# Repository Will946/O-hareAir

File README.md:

# O'Hare Air

A desktop air quality monitor shaped like a flower. It watches temperature, humidity, and air quality (eCO2/eTVOC/AQI-UBA) with a ScioSense ENS161 + ENS210, points a physical stepper-driven needle at the current rating, glows green-to-red through an RGB LED, and serves a full live dashboard over Wi-Fi with history and CSV export. No app, no cloud, no account.

---

## Where the name comes from

The name is taken from The Lorax (2012). In the film, Aloysius O'Hare is the mayor of Thneedville and the founder/CEO of "O'Hare Air," a company that sells bottled air to the town after industrial pollution ruined the natural air supply. This project borrows the name "O'Hare Air" for a device that measures real air quality.

---

## Table of contents

- [Features](#features)
- [How it all fits together](#how-it-all-fits-together)
- [Hardware — two PCB generations](#hardware--two-pcb-generations)
  - [V1 — ESP32-S3 dev-board shield](#v1--esp32-s3-dev-board-shield)
  - [V2 — custom ESP32-H2 module board](#v2--custom-esp32-h2-module-board)
  - [V1 vs V2 at a glance](#v1-vs-v2-at-a-glance)
- [Firmware](#firmware)
  - [Startup and timing](#startup-and-timing)
  - [How air quality is measured and calculated](#how-air-quality-is-measured-and-calculated)
  - [Temperature and humidity](#temperature-and-humidity)
  - [The needle](#the-needle)
  - [The LED](#the-led)
  - [History logging](#history-logging)
- [The web dashboard](#the-web-dashboard)
- [Flashing it yourself](#flashing-it-yourself)
- [Known limitations](#known-limitations)

---

## Features

- **Real air-quality sensing**: ScioSense ENS161 (eTVOC, eCO2, and an onboard 1-5 AQI-UBA rating) plus an ENS210 for temperature and humidity.
- **A physical gauge**: a 28BYJ-48 stepper motor sweeps a needle from 0° to 180° across five ratings: Excellent, Good, Moderate, Poor, Unhealthy.
- **A living LED**: a smooth green-to-red gradient that tracks the current rating, and a slow blue pulse while the sensor is still warming up.
- **A full web dashboard**: live readings, up to seven days of on-device history with min/avg/max, CSV export, and manual needle/LED control, all served directly from the board over Wi-Fi.
- **Two hardware generations**: a shield that plugs onto an off-the-shelf ESP32-S3 dev board (V1), and a from-scratch, coin-sized board built around a bare ESP32-H2 module (V2).
- **A 3D-printed flower enclosure**, because an air monitor sitting on your desk should look like it belongs there.

---

## How it all fits together

```
        ENS210 (temp/RH) ──┐
                            ├──► ESP32 ──► 28BYJ-48 stepper ──► needle (0°-180°)
        ENS161 (AQI-UBA,   ─┘      │
        eTVOC, eCO2)               ├──► RGB LED (green → yellow → orange → red)
                                    │
                                    └──► Wi-Fi ──► built-in web dashboard
                                              (Live / History / Needle tabs)
```

Both sensors sit on the same I2C bus. Every reading cycle, the firmware pulls temperature and humidity from the ENS210, feeds them to the ENS161 as environmental compensation (metal-oxide gas sensors need to know how hot and humid the air is to interpret resistance changes correctly), then reads the ENS161's eTVOC, eCO2, and AQI-UBA registers. AQI-UBA, the sensor's own 1-5 classification, is what drives the needle and the LED. Everything is also pushed out over the board's Wi-Fi web server so it's watchable from a phone or laptop in real time.

---

## Hardware — two PCB generations

### V1 — ESP32-S3 dev-board shield

V1 is a **shield**: a round board with two 2×22 headers (`J9`/`J10`) that plug directly onto an **ESP32-S3-DevKitC-1** dev board, using its pinout exactly. Rather than design a whole MCU circuit, V1 borrows the dev board's regulator, USB-to-serial bridge, and antenna, so the custom PCB only has to carry the sensors, the LED driver, and a 1.8 V rail.

**On the shield itself:**

| Ref | Part | Purpose |
|---|---|---|
| U1 | ENS161-BLGT | Air quality sensor (I2C `0x52`), eTVOC, eCO2, AQI-UBA |
| U2 | ENS210-LQFM | Temperature/humidity sensor (I2C `0x43`) |
| U3 | MCP1700T-1802E | Linear regulator, 3.3 V → 1.8 V for the ENS161's `VDD` rail |
| R1, R2 | 10 kΩ | I2C pull-ups (SCL/SDA) |
| C1–C6 | 0.1 µF / 10 µF | Decoupling for the sensors and the LED |
| Q1 | BSS138 | N-MOSFET level shifter, 3.3 V logic → 5 V for the LED data line |
| LED1 | IN-PI15TAT5R5G5B | A single addressable RGB LED |
| J1 | 3-pin socket | Breaks out 5 V / 3.3 V / LED data for the LED module |
| H1–H3, TP1 | — | Mounting holes and a test point |

The two headers expose every GPIO the dev board offers, but the sketch only actually uses a handful of them: `GPIO8`/`GPIO9` for I2C, `GPIO4`–`GPIO7` for the stepper's four ULN2003 driver inputs, and `GPIO48` for the dev board's own onboard RGB LED. 

Full schematic: [`OhareV1PCB/OhareV1Sch.pdf`](OhareV1PCB/OhareV1Sch.pdf). Manufacturing files (Gerbers) are in [`OhareV1PCB/Gerber.zip`](OhareV1PCB/Gerber.zip); KiCad source is [`OhareV1.kicad_pcb`](OhareV1PCB/OhareV1.kicad_pcb) / [`OhareV1.kicad_sch`](OhareV1PCB/OhareV1.kicad_sch).

### V2 — custom ESP32-H2 module board

V2 throws out the dev board entirely. Instead of two headers plugging into someone else's board, V2 puts an **ESP32-H2-MINI-1** module (a tiny, low-power Espressif module, not a full development board) directly on the PCB, along with its own USB-C connector and its own power regulation. The result is dramatically smaller: the whole "computer" fits in the footprint of the module itself, not a full dev-board-shaped hole in the middle of the design.

**On the V2 board:**

| Ref | Part | Purpose |
|---|---|---|
| U7 | ESP32-H2-MINI-1 | The microcontroller: BLE + 802.15.4 (Zigbee/Thread) radio, **no Wi-Fi** (see below) |
| U2 | ENS161 | Air quality sensor (I2C `0x52`) |
| U10 | ENS210 | Temperature/humidity sensor (I2C `0x43`) |
| U6 | AP2205 | 3.3 V regulator (the board's main "3V3 bus") |
| U5 | AP2120 | 1.8 V regulator, for the ENS161's `VDD` |
| P1 | USB-C receptacle | Power and native USB flashing (the H2 has built-in USB, no separate USB-serial chip needed) |
| D5 | TPD1E10B06 | ESD/surge protection on the USB data lines |
| R21, R22 | 5.1 kΩ | USB-C CC pull-downs, so the board correctly identifies itself as a 5 V sink to chargers and power banks |
| Q1 | BSS138 | Same level-shifting job as V1: 3.3 V logic to 5 V LED data |
| LED1, LED2, LED3 | IN-PI15TAT5R5G5B | **Three** addressable RGB LEDs (labeled Front Left / Front Right / Rear Right on the silkscreen), daisy-chained, instead of V1's single LED |
| S2 | Push button | BOOT (bootloader entry for flashing) |
| S3 | Push button | Reset |

Full schematic: [`OhareV2PCB/OhareV2Sch.pdf`](OhareV2PCB/OhareV2Sch.pdf); KiCad source is [`OhareV2.kicad_pcb`](OhareV2PCB/OhareV2.kicad_pcb) / [`OhareV2.kicad_sch`](OhareV2PCB/OhareV2.kicad_sch).

### V1 vs V2 at a glance

| | V1 | V2 |
|---|---|---|
| MCU | ESP32-S3-DevKitC-1 (full dev board, plugged in via headers) | ESP32-H2-MINI-1 (bare module, soldered directly to the PCB) |
| Radio | Wi-Fi + BLE | BLE + 802.15.4 (Zigbee/Thread); no Wi-Fi |
| Size | Dev-board-sized | A fraction of that; the module is the board |
| Power in | Through the dev board's own USB-C | Native USB-C directly on the PCB |
| LEDs | 1 (drives the dev board's onboard LED) | 3, individually placed under the enclosure's petals |
| Flashing | Dev board's onboard USB-to-serial bridge | Native USB on the H2 itself |
| Firmware status | **Fully supported**, this is what the current sketch targets | **Current firmware is supported on new version |

---

## Firmware

The active firmware is [`Code/OhareAir/OhareAir.ino`](Code/OhareAir/OhareAir.ino), an Arduino sketch built for the **ESP32-S3 (V1)**. It's written directly against the ENS161 and ENS210 datasheets: talking to both sensors over I2C, driving the stepper needle and RGB LED, and serving the whole web dashboard, all from a single self-contained sketch.

### Startup and timing

On power-up, both sensors initialize immediately, but **nothing is read for the first 3 minutes.** The ENS161 needs that long to reach a stable operating temperature; reading it earlier just produces noise. During this warm-up the LED pulses a slow blue instead of showing a color it can't back up yet, and the needle stays parked at 0°.

Once warm-up ends, the firmware takes **one reading per minute**. A flower on a desk doesn't need second-by-second air-quality updates, and a slower cadence keeps the I2C bus quieter.

Each reading cycle:
1. Read temperature and humidity from the ENS210.
2. Write those values to the ENS161's compensation registers (`TEMP_IN` / `RH_IN`), so its gas readings account for the current conditions.
3. Give the ENS161 a moment to fold that compensation into its next internal measurement.
4. Read eTVOC, eCO2, and AQI-UBA off the ENS161.
5. Feed everything into the 5-minute history accumulator.
6. If Auto mode is on, hand AQI-UBA to the needle logic.

### How air quality is measured and calculated

The ENS161 is a metal-oxide gas sensor: it doesn't count individual VOC molecules, it measures how much a heated sensing element's electrical resistance shifts when exposed to reactive gases, then converts that into three numbers over I2C:

- **eTVOC** (equivalent Total Volatile Organic Compounds, in ppb): the chip's estimate of total VOC concentration, calibrated against ethanol as a reference gas. This is the sensor's actual measurement; everything else is derived from it.
- **eCO2** (equivalent CO2, in ppm): not a real CO2 measurement. It's estimated from the same VOC signal, so it tracks eTVOC almost exactly and should be read as "how stale does the air smell," not literal CO2 concentration.
- **AQI-UBA** (1-5): the chip's own onboard hygienic rating, computed internally by ScioSense's proprietary algorithm from its eTVOC signal, using threshold bands published by Germany's Federal Environmental Agency (Umweltbundesamt, hence "UBA"):

  | AQI-UBA | Rating | Approx. eTVOC |
  |---|---|---|
  | 1 | Excellent | 0 – 65 ppb |
  | 2 | Good | 65 – 220 ppb |
  | 3 | Moderate | 220 – 650 ppb |
  | 4 | Poor | 650 – 2,200 ppb |
  | 5 | Unhealthy | 2,200 ppb+ |

**AQI-UBA is what drives the needle and the LED**, rather than a hand-built formula. eTVOC and eCO2 are still read, displayed, and logged, but the rating itself comes straight from the ENS161's own proprietary onboard algorithm: ScioSense's classification, computed inside the chip from its own internal, self-compensating signal, not something calculated in software afterward. The trade-off is that AQI-UBA can't be corrected or offset after the fact the way a software-calculated number could; whatever the chip decides, the firmware trusts.

### Temperature and humidity

Raw ENS210 output is corrected by a fixed offset (`TEMP_OFFSET_C`, currently 5.56 °C) to account for the board's own self-heating from the MCU and Wi-Fi radio; an uncorrected reading on this hardware runs noticeably warmer than the actual room. This is a per-board constant; if you build your own, re-measure it against a reference thermometer and adjust.

### The needle

A 28BYJ-48 stepper motor (through a ULN2003 driver board) sweeps a needle across a 180° arc:

| Rating | Angle |
|---|---|
| Excellent | 0° |
| Good | 90° |
| Moderate | 115° |
| Poor | 140° |
| Unhealthy | 180° |

To avoid the needle twitching back and forth when AQI-UBA hovers right at a boundary, a new rating has to show up in **two readings in a row** (about two minutes) before the needle actually moves. Position is tracked in software as a step count from a zeroed home position. There's no physical limit switch, so the needle has to be manually set to 0° before every power-up; if the board resets while the needle is elsewhere, the software's idea of "0°" and the needle's real position will disagree until it's re-zeroed by hand.

### The LED

The LED (a single onboard RGB LED on V1; three chained LEDs, wired for that, on V2's hardware) fades smoothly between colors rather than snapping: green at AQI-UBA 1, sliding through yellow and orange, to red at AQI-UBA 5. During warm-up, before any reading exists, it pulses a slow blue instead. Brightness (0/10/30/60/100%) is adjustable from the dashboard and resets to 60% on every reboot; it isn't saved to flash.

### History logging

Every 5 minutes, the firmware saves one entry (the minimum, average, and maximum of temperature, humidity, AQI-UBA, eCO2, and eTVOC over that window) into a ring buffer sized for **7 days** (2,016 entries), packed into a fixed 32-byte record per entry. **This history lives entirely in RAM, not flash**; it's lost on every reboot or power cycle. A window where a sensor read failed is stored as an explicit "no data" marker rather than a guessed value, so a bad reading never silently drags down an average.

---

## The web dashboard

The board runs its own web server (`WebServer.h`) and serves a self-contained single-page dashboard: no external app, no cloud round-trip. Connect it to Wi-Fi, open its IP address in a browser, and you get three tabs:

**Live**

The current AQI-UBA rating as a big color-coded number and name, a five-segment scale showing where it sits, temperature/humidity/eCO2/eTVOC cards, and three live-updating charts (temperature & humidity, AQI-UBA, and gas levels) that add one point per new reading, not per page refresh, so leaving the tab open doesn't flood the chart with duplicate points. LED brightness controls live here too.

**History**

The same charts, but built from the on-device 5-minute history instead of the live buffer, with a range selector (6 hours to 7 days) and CSV export.

**Needle**

Manual control: an Auto/Manual toggle, a reference table of which AQI-UBA rating maps to which angle, one-tap "go to angle" buttons for each rating, a free-form rotate-by-degrees input, and motor speed adjustment.

**Endpoints**, for anyone scripting against it directly:

| Endpoint | Purpose |
|---|---|
| `GET /status` | Current reading, needle state, and device status as JSON |
| `GET /history?n=N` | The newest N history entries as compact JSON |
| `GET /rotate?degrees=X` | Rotate the needle by X° (switches to Manual) |
| `GET /goto?degrees=X` | Move the needle to an absolute angle (switches to Manual) |
| `GET /mode?auto=0\|1` | Switch between Auto and Manual |
| `GET /speed?direction=faster\|slower` | Adjust stepper speed |
| `GET /brightness?pct=X` | Set LED brightness, 0–100 |

---

## Flashing it yourself

1. Arduino IDE with the ESP32 board package installed, targeting an ESP32-S3 board (V1 hardware).
2. Install the **Adafruit NeoPixel** library. `Wire`, `WiFi`, and `WebServer` ship with the ESP32 core.
3. Open [`Code/OhareAir/OhareAir.ino`](Code/OhareAir/OhareAir.ino) and fill in your Wi-Fi credentials:
```cpp
   const char* ssid = "";
   const char* password = "";
```
4. Flash it, then open the Serial Monitor at 115200 baud; it prints the board's IP address once connected.
5. Set the needle to its physical 0° position before powering on, since the firmware has no way to detect where it actually is.
6. Open that IP address in a browser on the same network.

---

## Known limitations

- **Highly temperature- and humidity-dependent.** The ENS161 is a metal-oxide gas sensor: its readings shift with the temperature and humidity it's told to compensate for, and the board's own self-heating (from the MCU and Wi-Fi radio) pushes the ENS210's raw temperature well above the actual room temperature. That's corrected with a fixed offset (`TEMP_OFFSET_C`) tuned for this specific board; a different enclosure, a different MCU, or even just a different ambient environment can shift the true offset enough that eTVOC, eCO2, and AQI-UBA all read differently than they would with perfect compensation.
- **History doesn't survive a reboot.** It's RAM-only; a power cycle clears it.
- **The needle has no home sensor.** It has to be manually zeroed before every power-up.
- **Wi-Fi credentials are hardcoded** in the sketch, not configurable from the dashboard.
- **No OTA updates**: reflashing means plugging in over USB, which means having to disassemble the enclosure to access the port.

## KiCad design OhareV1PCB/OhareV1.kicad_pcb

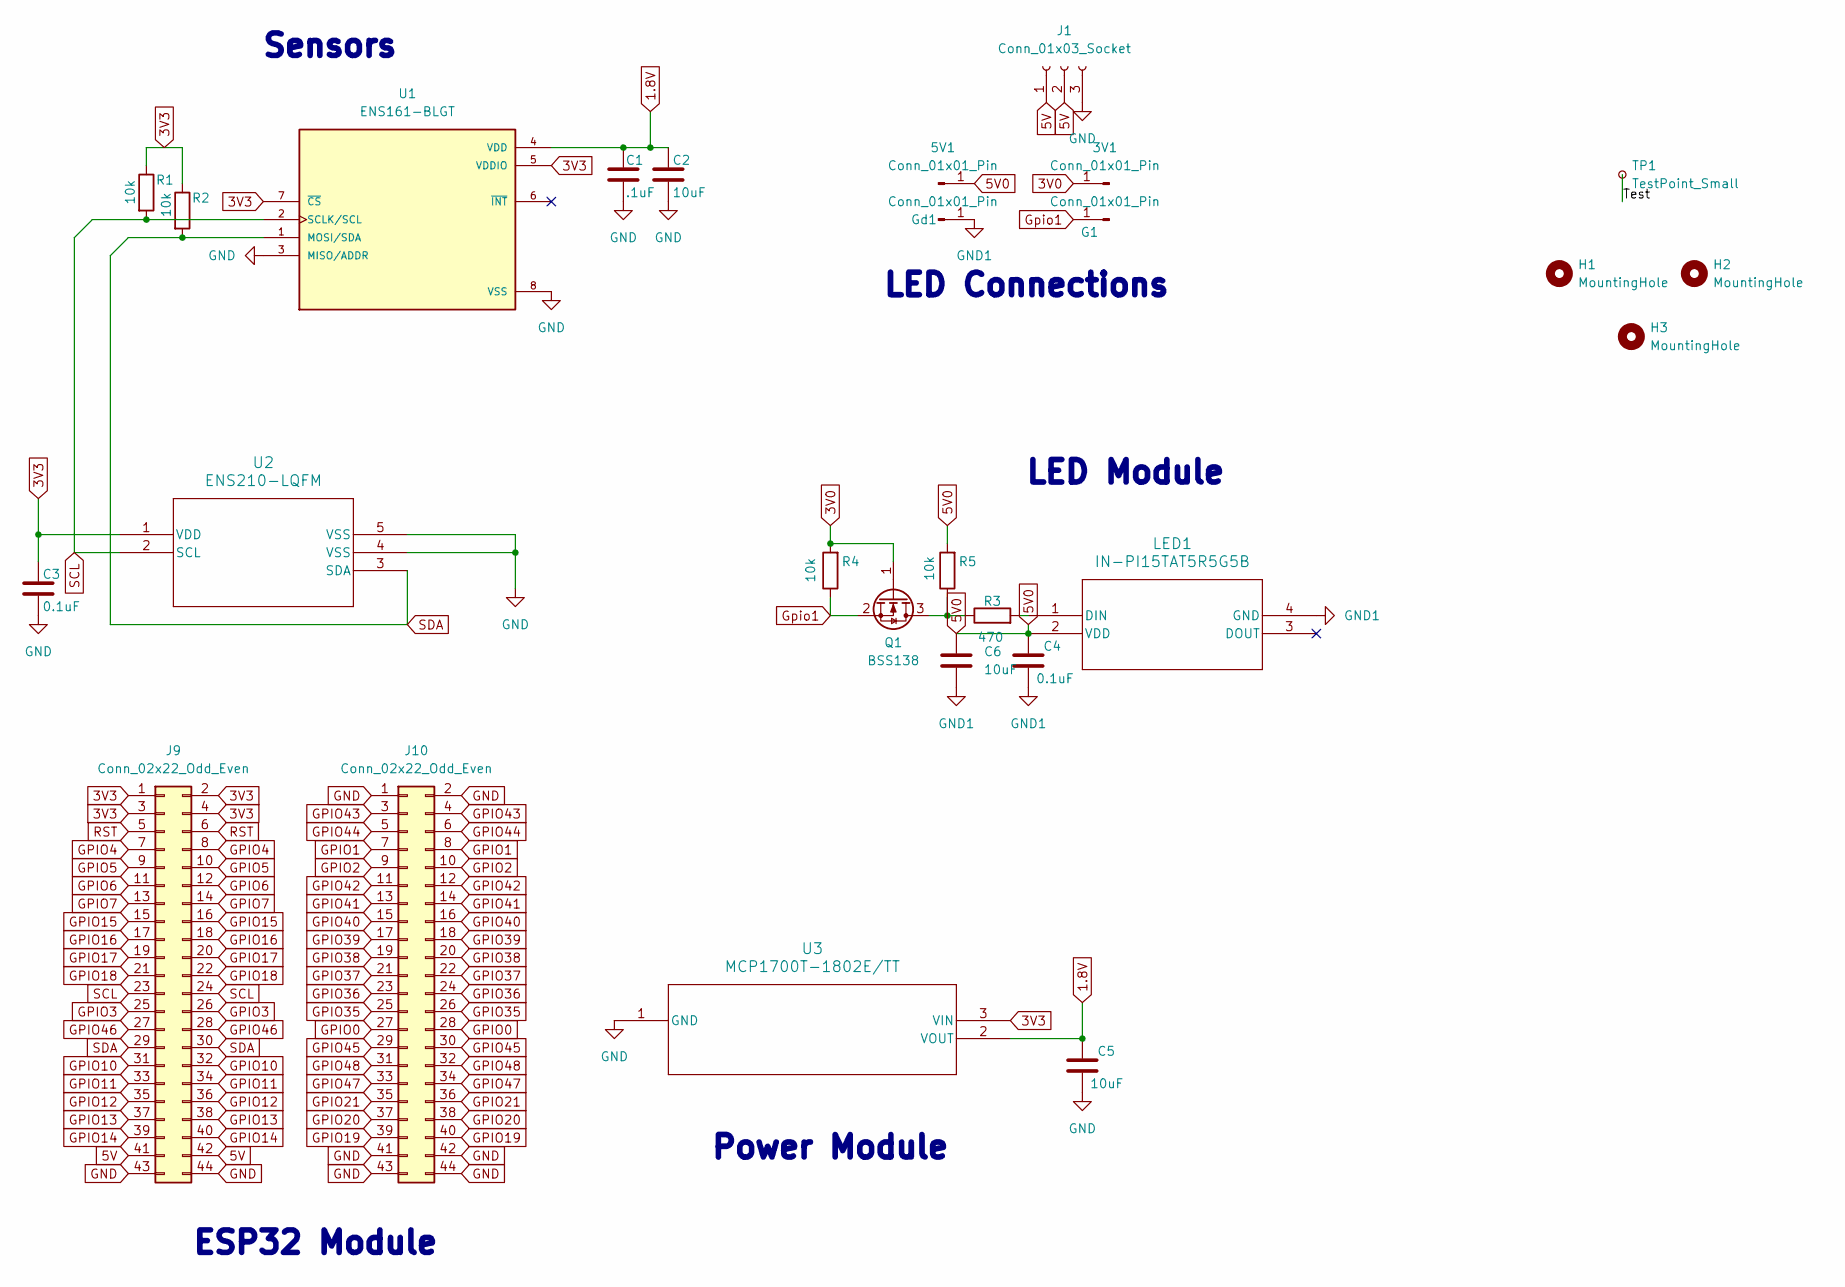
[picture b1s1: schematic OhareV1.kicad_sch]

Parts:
3V1, 5V1: Conn_01x01_Pin; PinHeader_1x01_P1.27mm_Vertical
C1: .1uF; C_0805_2012Metric_Pad1.18x1.45mm_HandSolder
C2, C5, C6: 10uF; C_0805_2012Metric_Pad1.18x1.45mm_HandSolder
C3, C4: 0.1uF; C_0805_2012Metric_Pad1.18x1.45mm_HandSolder
G1: Conn_01x01_Pin; PinHeader_1x01_P1.27mm_Vertical
Gd1: Conn_01x01_Pin; PinHeader_1x01_P1.27mm_Vertical
H1, H2, H3: MountingHole; MountingHole_3.2mm_M3
J1: Conn_01x03_Socket; PinHeader_1x03_P1.27mm_Vertical
J9, J10: Conn_02x22_Odd_Even; PinHeader_2x22_P2.54mm_Vertical
LED1: IN-PI15TAT5R5G5B; IN-PI15_INL
Q1: BSS138; SOT-23_3L_ONS-L
R1, R2, R4, R5: 10k; R_0805_2012Metric_Pad1.20x1.40mm_HandSolder
R3: 470; R_0805_2012Metric_Pad1.20x1.40mm_HandSolder
TP1: TestPoint_Small; TestPoint_Pad_1.0x1.0mm
U1: ENS161-BLGT; XDCR_ENS161-BLGT; PARTREV 1.3; DigiKey_Part_Number 2618-ENS161-BLGTCT-ND
U2: ENS210-LQFM; SON-04-ENS210_2X2_AMS-L
U3: MCP1700T-1802E/TT; SOT-23_MC_MCH-L

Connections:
1.8V: C1.1, C2.1, C5.1, U1.4 (VDD), U3.2 (VOUT)
3V0: 3V1.1, Q1.1 (G), R4.2
3V3: C3.1, J9.1, J9.2, J9.3, J9.4, R1.1, R2.1, U1.5 (VDDIO), U1.7 (~CS), U2.1 (VDD), U3.3 (VIN)
5V: J1.1, J1.2, J9.41, J9.42
5V0: 5V1.1, C4.1, C6.1, LED1.2 (VDD), R5.2
/Test: TP1.1
GND: C1.2, C2.2, C3.2, C5.2, J1.3, J9.43, J9.44, J10.1, J10.2, J10.41, J10.42, J10.43, J10.44, U1.3 (MISO/ADDR), U1.8 (VSS), U1.9 (VSS), U2.4 (VSS), U2.5 (VSS), U3.1 (GND)
GND1: C4.2, C6.2, Gd1.1, LED1.4 (GND)
GPIO0: J10.27, J10.28
GPIO1: J10.7, J10.8
GPIO2: J10.9, J10.10
GPIO3: J9.25, J9.26
GPIO4: J9.7, J9.8
GPIO5: J9.9, J9.10
GPIO6: J9.11, J9.12
GPIO7: J9.13, J9.14
GPIO10: J9.31, J9.32
GPIO11: J9.33, J9.34
GPIO12: J9.35, J9.36
GPIO13: J9.37, J9.38
GPIO14: J9.39, J9.40
GPIO15: J9.15, J9.16
GPIO16: J9.17, J9.18
GPIO17: J9.19, J9.20
GPIO18: J9.21, J9.22
GPIO19: J10.39, J10.40
GPIO20: J10.37, J10.38
GPIO21: J10.35, J10.36
GPIO35: J10.25, J10.26
GPIO36: J10.23, J10.24
GPIO37: J10.21, J10.22
GPIO38: J10.19, J10.20
GPIO39: J10.17, J10.18
GPIO40: J10.15, J10.16
GPIO41: J10.13, J10.14
GPIO42: J10.11, J10.12
GPIO43: J10.3, J10.4
GPIO44: J10.5, J10.6
GPIO45: J10.29, J10.30
GPIO46: J9.27, J9.28
GPIO47: J10.33, J10.34
GPIO48: J10.31, J10.32
Gpio1: G1.1, Q1.2 (S), R4.1
unnamed: LED1.1 (DIN), R3.2
unnamed: Q1.3 (D), R3.1, R5.1
RST: J9.5, J9.6

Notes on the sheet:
LED Connections
ESP32 Module
LED Module
Power Module
Sensors

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
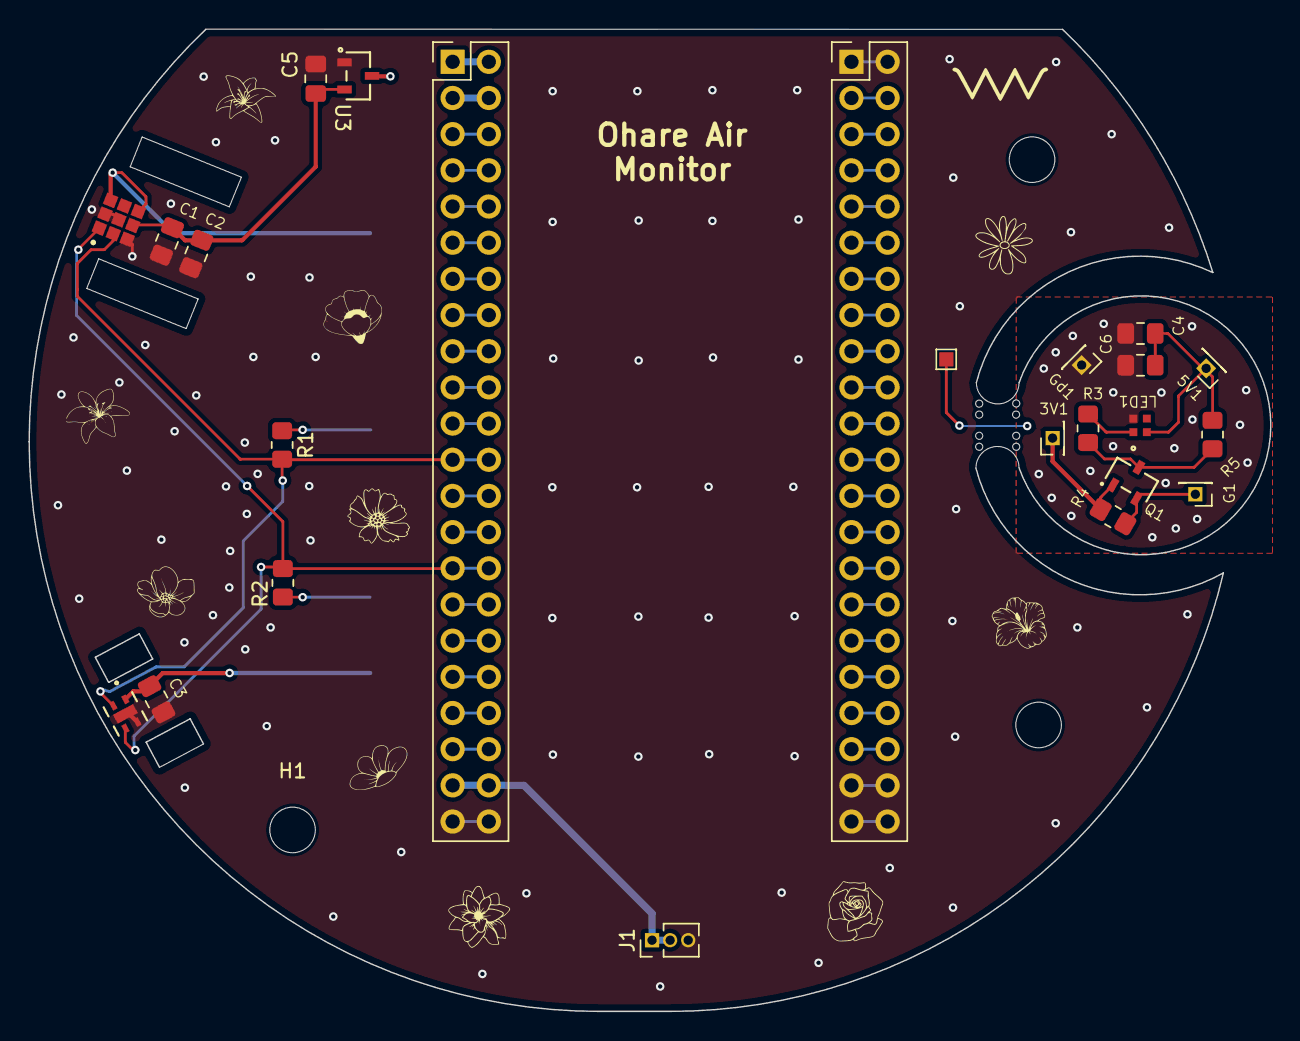
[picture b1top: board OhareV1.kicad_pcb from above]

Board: 2 copper layers, 87.2 x 69.0 mm, 28 parts (0 on the bottom side), 47 nets.

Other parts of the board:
mouse-bite-3mm-6mm: VAL**; mouse-bite-3mm-6mm

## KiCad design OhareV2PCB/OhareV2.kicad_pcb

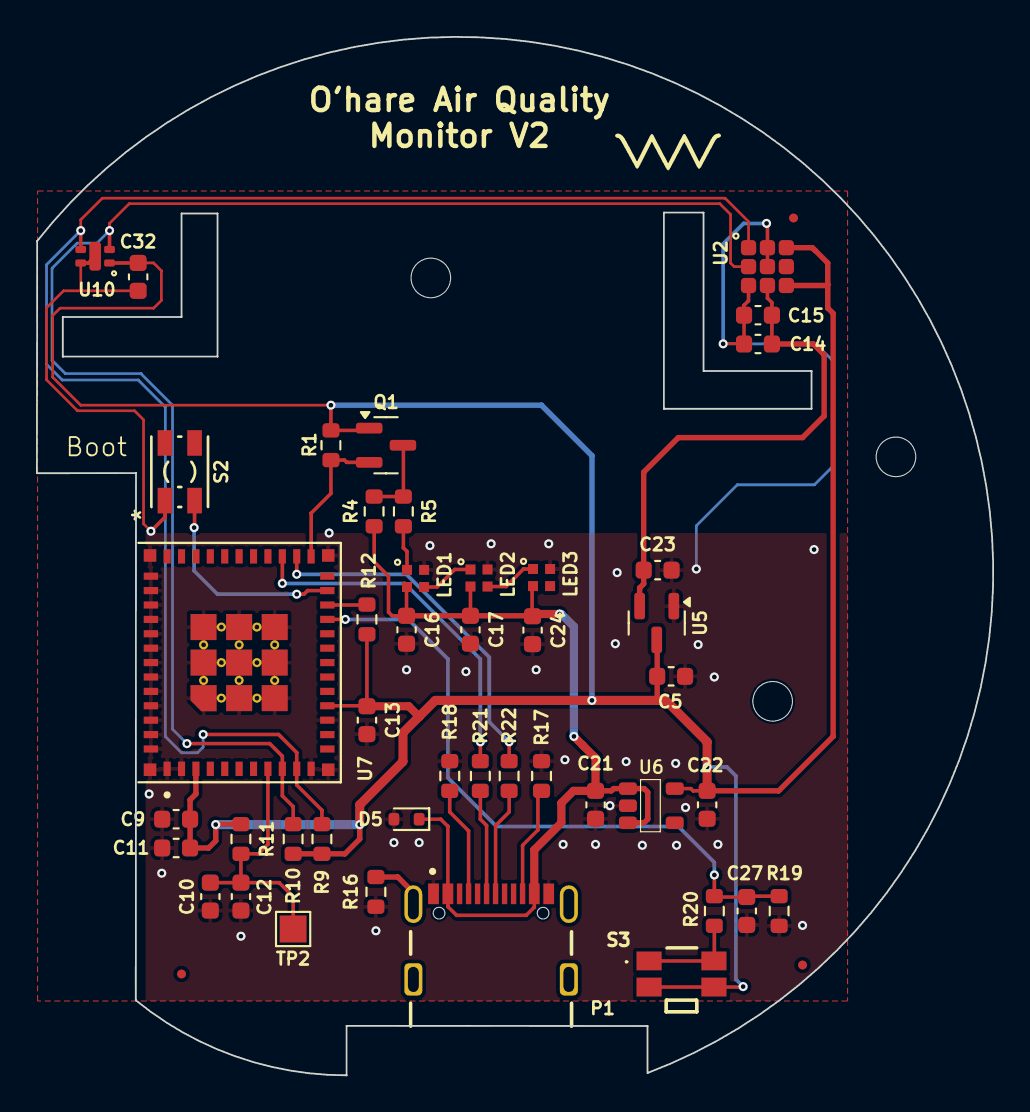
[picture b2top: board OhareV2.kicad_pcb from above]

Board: 2 copper layers, 53.1 x 57.7 mm, 44 parts (0 on the bottom side), 23 nets.

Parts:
C5, C10: 1uF; C_0603_1608Metric
C9: 47uF; C_0603_1608Metric
C11, C12, C13, C15, C16, C17, C24, C27, C32: 0.1uF; C_0603_1608Metric
C14, C21, C22, C23: 10uF; C_0603_1608Metric
D5: TPD1E10B06; D_SOD-523
LED1, LED2, LED3: IN-PI15TAT5R5G5B; IN-PI15_INL
P1: USB_C_Plug_USB2.0; GCT_USB4105-GF-A
Q1: BSS138; SOT-23
R1, R4, R11, R12: 10K; R_0603_1608Metric
R5: 470; R_0603_1608Metric
R9, R10, R20: 10k; R_0603_1608Metric
R16: 1M; R_0603_1608Metric
R17, R18: 5K1; R_0603_1608Metric
R19: 100k; R_0603_1608Metric
R21, R22: 22; R_0603_1608Metric
S2: SWITCH_0SMTRLFS
S3: TL1016AAF220QG
TP2: TestPoint; TestPoint_Pad_1.5x1.5mm
U2: ENS161
U5: AP2120; SOT-23
U6: AP2205; AP2204
U7: ESP32-H2-MINI-1; MODULE_ESP32-H2-MINI-1-H2
U10: ENS210

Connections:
+1V8: C14.1, C15.1, C23.1, U2.4 (VDD), U5.2 (VOUT)
+3V3: C5.1, C9.1, C11.1, C13.1, C22.1, C32.1, Q1.1 (G), R1.2, R9.1, R10.1, R11.1, R12.2, S3.3, S3.4, U2.5 (VDDIO), U2.7 (CSn), U5.3 (VIN), U6.5 (VOUT), U7.3 (3v3), U7.15 (VBAT), U10.1 (VDD)
+5VD: C16.1, C17.1, C21.1, C24.1, D5.1, LED1.2 (VDD), LED2.2 (VDD), LED3.2 (VDD), P1.A4 (VBUS), P1.A9 (VBUS), R4.2, U6.1 (VIN), U6.3 (EN)
/CP_EN: C10.1, C12.1, R11.2, TP2.1, U7.8 (EN)
/SCL: R10.2, U2.2 (SCL), U7.9 (IO0), U10.2 (SCL)
/SDA: R9.2, U2.1 (SDA), U7.10 (IO01), U10.3 (SDA)
/USB_D+: R21.1, U7.27 (IO27)
/USB_D-: R22.2, U7.26 (IO26)
GND: C5.2, C9.2, C10.2, C11.2, C12.2, C13.2, C14.2, C15.2, C16.2, C17.2, C21.2, C22.2, C23.2, C24.2, C27.2, C32.2, D5.2, LED1.4 (GND), LED2.4 (GND), LED3.4 (GND), P1.A1 (GND), P1.A12 (GND), R16.2, R17.2, R18.2, R19.2, S2.1, U2.3 (ADDR), U2.8 (VSS), U2.9 (VSS), U5.1 (GND), U6.2 (GND), U7.1 (GND), U7.2 (GND), U7.11 (GND), U7.14 (GND), U7.36 (GND), U7.37 (GND), U7.38 (GND), U7.39 (GND), U7.40 (GND), U7.41 (GND), U7.42 (GND), U7.43 (GND), U7.44 (GND), U7.45 (GND), U7.46 (GND), U7.47 (GND), U7.48 (GND), U7.49 (EPAD), U7.50 (GND), U7.51 (GND), U7.52 (GND), U7.53 (GND), U10.4 (VSS), U10.5 (VSS)
unnamed: LED1.1 (DIN), R5.2
unnamed: LED1.3 (DOUT), LED2.1 (DIN)
unnamed: LED2.3 (DOUT), LED3.1 (DIN)
unnamed: P1.A5 (CC), R18.1
unnamed: P1.A6 (D+), R21.2
unnamed: P1.A7 (D-), R22.1
unnamed: P1.S1 (SHIELD), R16.1
unnamed: P1.B5 (VCONN), R17.1
unnamed: Q1.3 (D), R4.1, R5.1
unnamed: Q1.2 (S), R1.1, U7.25 (IO25)
unnamed: R20.2, S3.1, S3.2
unnamed: R12.1, U7.22 (IO08)
unnamed: S2.2, U7.23 (IO9)
unnamed: C27.1, R19.1, R20.1, U7.21 (IO11)
